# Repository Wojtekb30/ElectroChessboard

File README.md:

# ElectroChessboard
Electronic chessboard

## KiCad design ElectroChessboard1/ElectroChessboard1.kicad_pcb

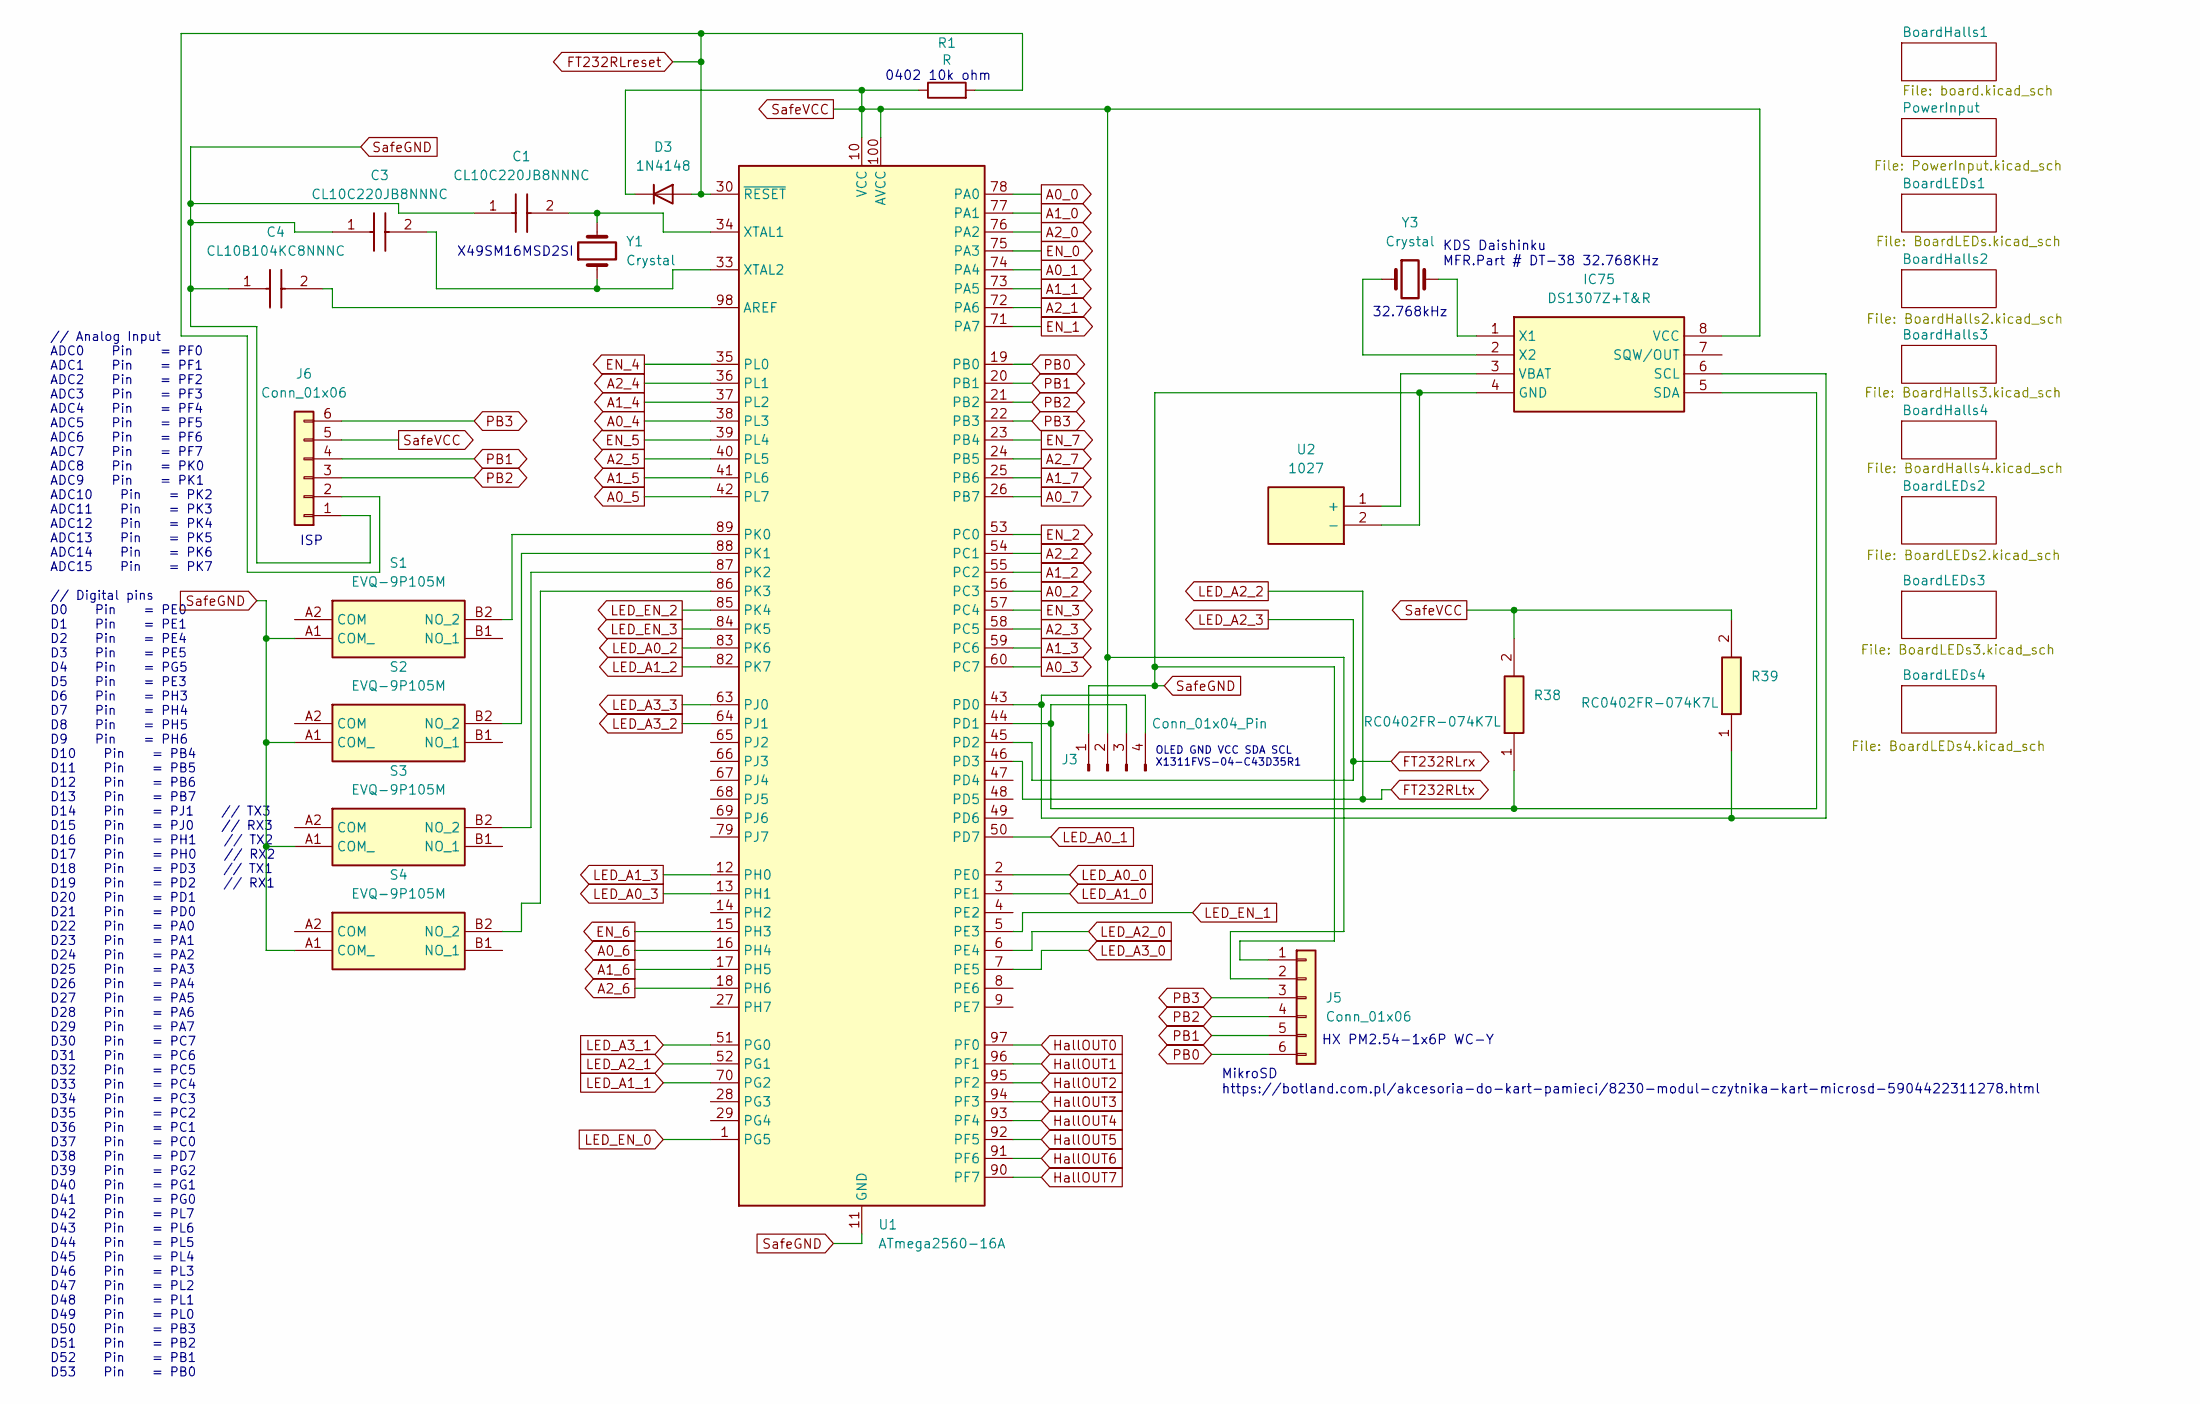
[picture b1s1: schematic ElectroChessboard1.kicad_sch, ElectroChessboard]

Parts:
C1, C3: CL10C220JB8NNNC; CAPC1608X90N; Mouser Part Number 187-CL10C220JB8NNNC
C4: CL10B104KC8NNNC; CAPC1608X90N; Mouser Part Number 187-CL10B104KC8NNNC
D3: 1N4148; D_SOD-123
IC75: DS1307Z+T&R; SOIC127P600X175-8N; Mouser Part Number 700-DS1307ZT&R
J3: Conn_01x04_Pin; PinSocket_1x04_P1.27mm_Vertical_SMD_Pin1Right
J5: Conn_01x06; PinSocket_1x06_P2.54mm_Horizontal
J6: Conn_01x06; PinSocket_1x06_P2.00mm_Vertical_SMD_Pin1Right
R1: R; R_0402_1005Metric
R38, R39: RC0402FR-074K7L; RESC1005X40N; Manufacturer_Part_Number RC0402FR-074K7L; Mouser Part Number 603-RC0402FR-074K7L
S1, S2, S3, S4: EVQ-9P105M; EVQ9P105M; Mouser Part Number 667-EVQ-9P105M
U1: ATmega2560-16A; TQFP-100_14x14mm_P0.5mm
U2: 1027; Mouser Part Number 534-1027
Y1: Crystal; Crystal_SMD_HC49-SD
Y3: Crystal; Crystal_C38-LF_D3.0mm_L8.0mm_Vertical

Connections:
A0_0: U1.78 (PA0); also elsewhere on the board
A0_1: U1.74 (PA4); also elsewhere on the board
A0_2: U1.56 (PC3); also elsewhere on the board
A0_3: U1.60 (PC7); also elsewhere on the board
A0_4: U1.38 (PL3); also elsewhere on the board
A0_5: U1.42 (PL7); also elsewhere on the board
A0_6: U1.16 (PH4); also elsewhere on the board
A0_7: U1.26 (PB7); also elsewhere on the board
A1_0: U1.77 (PA1); also elsewhere on the board
A1_1: U1.73 (PA5); also elsewhere on the board
A1_2: U1.55 (PC2); also elsewhere on the board
A1_3: U1.59 (PC6); also elsewhere on the board
A1_4: U1.37 (PL2); also elsewhere on the board
A1_5: U1.41 (PL6); also elsewhere on the board
A1_6: U1.17 (PH5); also elsewhere on the board
A1_7: U1.25 (PB6); also elsewhere on the board
A2_0: U1.76 (PA2); also elsewhere on the board
A2_1: U1.72 (PA6); also elsewhere on the board
A2_2: U1.54 (PC1); also elsewhere on the board
A2_3: U1.58 (PC5); also elsewhere on the board
A2_4: U1.36 (PL1); also elsewhere on the board
A2_5: U1.40 (PL5); also elsewhere on the board
A2_6: U1.18 (PH6); also elsewhere on the board
A2_7: U1.24 (PB5); also elsewhere on the board
EN_0: U1.75 (PA3); also elsewhere on the board
EN_1: U1.71 (PA7); also elsewhere on the board
EN_2: U1.53 (PC0); also elsewhere on the board
EN_3: U1.57 (PC4); also elsewhere on the board
EN_4: U1.35 (PL0); also elsewhere on the board
EN_5: U1.39 (PL4); also elsewhere on the board
EN_6: U1.15 (PH3); also elsewhere on the board
EN_7: U1.23 (PB4); also elsewhere on the board
FT232RLreset: D3.2 (A), J6.2, R1.2, U1.30 (~RESET); also elsewhere on the board
HallOUT0: U1.97 (PF0); also elsewhere on the board
HallOUT1: U1.96 (PF1); also elsewhere on the board
HallOUT2: U1.95 (PF2); also elsewhere on the board
HallOUT3: U1.94 (PF3); also elsewhere on the board
HallOUT4: U1.93 (PF4); also elsewhere on the board
HallOUT5: U1.92 (PF5); also elsewhere on the board
HallOUT6: U1.91 (PF6); also elsewhere on the board
HallOUT7: U1.90 (PF7); also elsewhere on the board
LED_A0_0: U1.2 (PE0); also elsewhere on the board
LED_A0_1: U1.50 (PD7); also elsewhere on the board
LED_A0_2: U1.83 (PK6); also elsewhere on the board
LED_A0_3: U1.13 (PH1); also elsewhere on the board
LED_A1_0: U1.3 (PE1); also elsewhere on the board
LED_A1_1: U1.70 (PG2); also elsewhere on the board
LED_A1_2: U1.82 (PK7); also elsewhere on the board
LED_A1_3: U1.12 (PH0); also elsewhere on the board
LED_A2_0: U1.6 (PE4); also elsewhere on the board
LED_A2_1: U1.52 (PG1); also elsewhere on the board
LED_A3_0: U1.7 (PE5); also elsewhere on the board
LED_A3_1: U1.51 (PG0); also elsewhere on the board
LED_A3_2: U1.64 (PJ1); also elsewhere on the board
LED_A3_3: U1.63 (PJ0); also elsewhere on the board
LED_EN_0: U1.1 (PG5); also elsewhere on the board
LED_EN_1: U1.5 (PE3); also elsewhere on the board
LED_EN_2: U1.85 (PK4); also elsewhere on the board
LED_EN_3: U1.84 (PK5); also elsewhere on the board
unnamed: IC75.6 (SCL), J3.4, R39.1, U1.43 (PD0)
unnamed: IC75.5 (SDA), J3.3, R38.1, U1.44 (PD1)
unnamed: IC75.3 (VBAT), U2.1 (+)
unnamed: IC75.1 (X1), Y3.2
unnamed: IC75.2 (X2), Y3.1
unnamed: S1.B2 (NO_2), U1.89 (PK0)
unnamed: S2.B2 (NO_2), U1.88 (PK1)
unnamed: S3.B2 (NO_2), U1.87 (PK2)
unnamed: S4.B2 (NO_2), U1.86 (PK3)
unnamed: C4.2, U1.98 (AREF)
unnamed: C1.2, U1.34 (XTAL1), Y1.2
unnamed: C3.2, U1.33 (XTAL2), Y1.1
PB0: J5.6, U1.19 (PB0)
PB1: J5.5, J6.4, U1.20 (PB1)
PB2: J5.4, J6.3, U1.21 (PB2)
PB3: J5.3, J6.6, U1.22 (PB3)
SafeGND: C1.1, C3.1, C4.1, IC75.4 (GND), J3.1, J5.1, J6.1, S1.A1 (COM_), S2.A1 (COM_), S3.A1 (COM_), S4.A1 (COM_), U1.11 (GND), U1.32 (GND), U1.62 (GND), U1.81 (GND), U1.99 (GND), U2.2 (-); also elsewhere on the board
SafeVCC: D3.1 (K), IC75.8 (VCC), J3.2, J5.2, J6.5, R1.1, R38.2, R39.2, U1.10 (VCC), U1.31 (VCC), U1.61 (VCC), U1.80 (VCC), U1.100 (AVCC); also elsewhere on the board

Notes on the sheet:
// Analog Input ADC0 Pin = PF0 ADC1 Pin = PF1 ADC2 Pin = PF2 ADC3 Pin = PF3 ADC4 Pin = PF4 ADC5 Pin = PF5 ADC6 Pin = PF6 ADC7 Pin = PF7 ADC8 Pin = PK0 ADC9 Pin = PK1 ADC10 Pin = PK2 ADC11 Pin = PK3 ADC12 Pin = PK4 ADC13 Pin = PK5 ADC14 Pin = PK6 ADC15 Pin = PK7 // Digital pins D0 Pin = PE0 D1 Pin =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
32.768kHz
X49SM16MSD2SI
0402 10k ohm
MikroSD https://botland.com.pl/akcesoria-do-kart-pamieci/8230-modul-czytnika-kart-microsd-5904422311278.html
ISP
HX PM2.54-1x6P WC-Y
KDS Daishinku MFR.Part # DT-38 32.768KHz
OLED GND VCC SDA SCL X1311FVS-04-C43D35R1

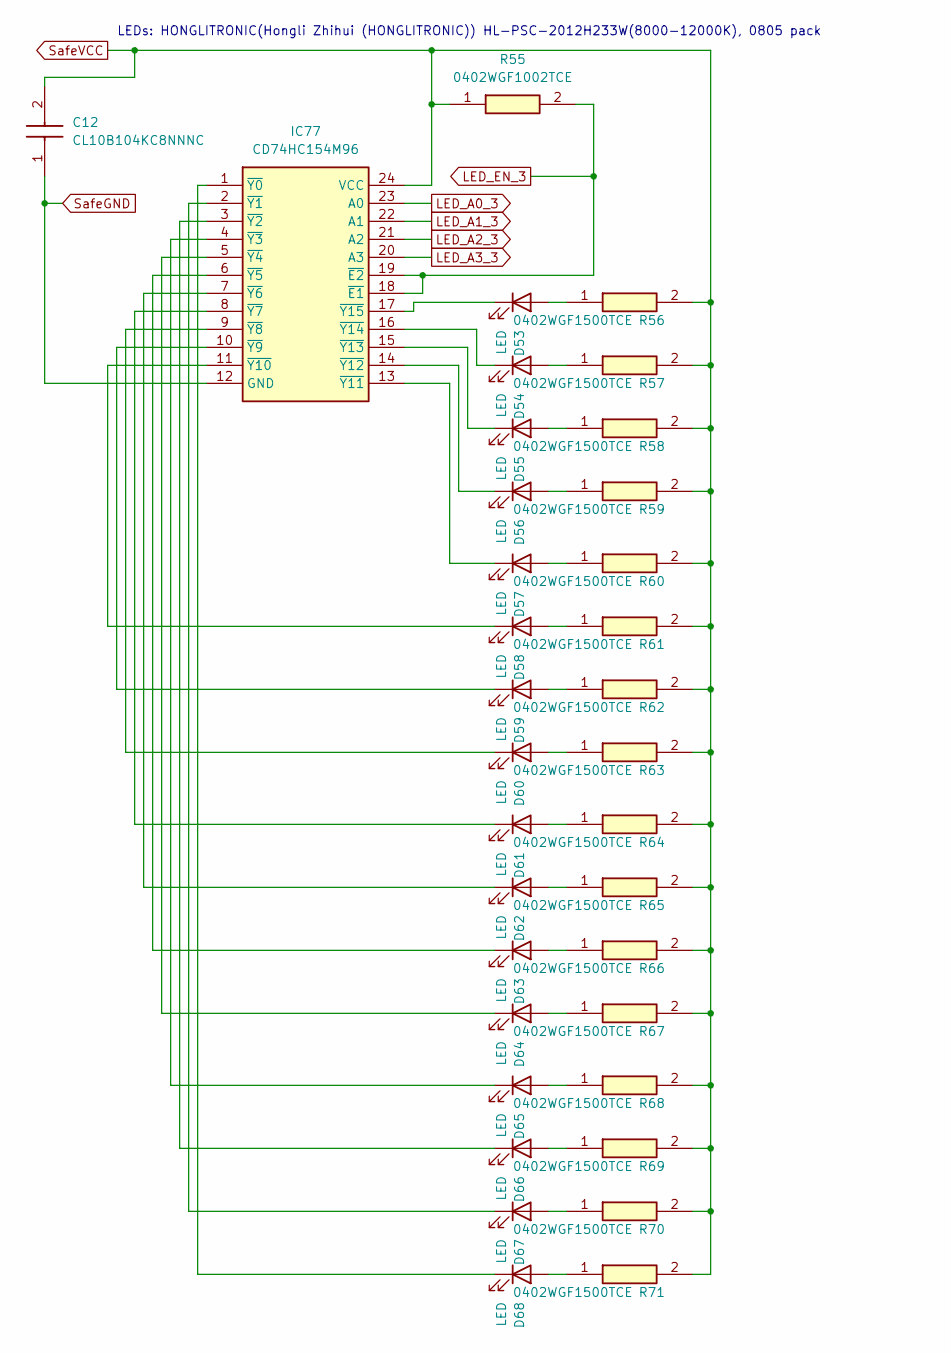
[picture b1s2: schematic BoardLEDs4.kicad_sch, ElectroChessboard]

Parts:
C12: CL10B104KC8NNNC; CAPC1608X90N; Mouser Part Number 187-CL10B104KC8NNNC
D53, D54, D55, D56, D57, D58, D59, D60, D61, D62, D63, D64, D65, D66, D67, D68: LED; LED_0805_2012Metric
IC77: CD74HC154M96; SOIC127P1030X265-24N; Mouser Part Number 595-CD74HC154M96
R55: 0402WGF1002TCE; RESC1005X40N; Mouser Part Number 303-0402WGF1002TCE
R56, R57, R58, R59, R60, R61, R62, R63, R64, R65, R66, R67, R68, R69, R70, R71: 0402WGF1500TCE; RESC1005X40N; Manufacturer_Part_Number 0402WGF1500TCE

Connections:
LED_A0_3: IC77.23 (A0); also elsewhere on the board
LED_A1_3: IC77.22 (A1); also elsewhere on the board
LED_A3_3: IC77.20 (A3); also elsewhere on the board
LED_EN_3: IC77.18 (~E1), IC77.19 (~E2), R55.2; also elsewhere on the board
unnamed: D53.2 (A), R56.1
unnamed: D53.1 (K), IC77.17 (~Y15)
unnamed: D54.2 (A), R57.1
unnamed: D54.1 (K), IC77.16 (~Y14)
unnamed: D55.2 (A), R58.1
unnamed: D55.1 (K), IC77.15 (~Y13)
unnamed: D56.2 (A), R59.1
unnamed: D56.1 (K), IC77.14 (~Y12)
unnamed: D57.2 (A), R60.1
unnamed: D57.1 (K), IC77.13 (~Y11)
unnamed: D58.2 (A), R61.1
unnamed: D58.1 (K), IC77.11 (~Y10)
unnamed: D59.2 (A), R62.1
unnamed: D59.1 (K), IC77.10 (~Y9)
unnamed: D60.2 (A), R63.1
unnamed: D60.1 (K), IC77.9 (~Y8)
unnamed: D61.2 (A), R64.1
unnamed: D61.1 (K), IC77.8 (~Y7)
unnamed: D62.2 (A), R65.1
unnamed: D62.1 (K), IC77.7 (~Y6)
unnamed: D63.2 (A), R66.1
unnamed: D63.1 (K), IC77.6 (~Y5)
unnamed: D64.2 (A), R67.1
unnamed: D64.1 (K), IC77.5 (~Y4)
unnamed: D65.2 (A), R68.1
unnamed: D65.1 (K), IC77.4 (~Y3)
unnamed: D66.2 (A), R69.1
unnamed: D66.1 (K), IC77.3 (~Y2)
unnamed: D67.2 (A), R70.1
unnamed: D67.1 (K), IC77.2 (~Y1)
unnamed: D68.2 (A), R71.1
unnamed: D68.1 (K), IC77.1 (~Y0)
SafeGND: C12.1, IC77.12 (GND); also elsewhere on the board
SafeVCC: C12.2, IC77.24 (VCC), R55.1, R56.2, R57.2, R58.2, R59.2, R60.2, R61.2, R62.2, R63.2, R64.2, R65.2, R66.2, R67.2, R68.2, R69.2, R70.2, R71.2; also elsewhere on the board

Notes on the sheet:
LEDs: HONGLITRONIC(Hongli Zhihui (HONGLITRONIC)) HL-PSC-2012H233W(8000-12000K), 0805 pack

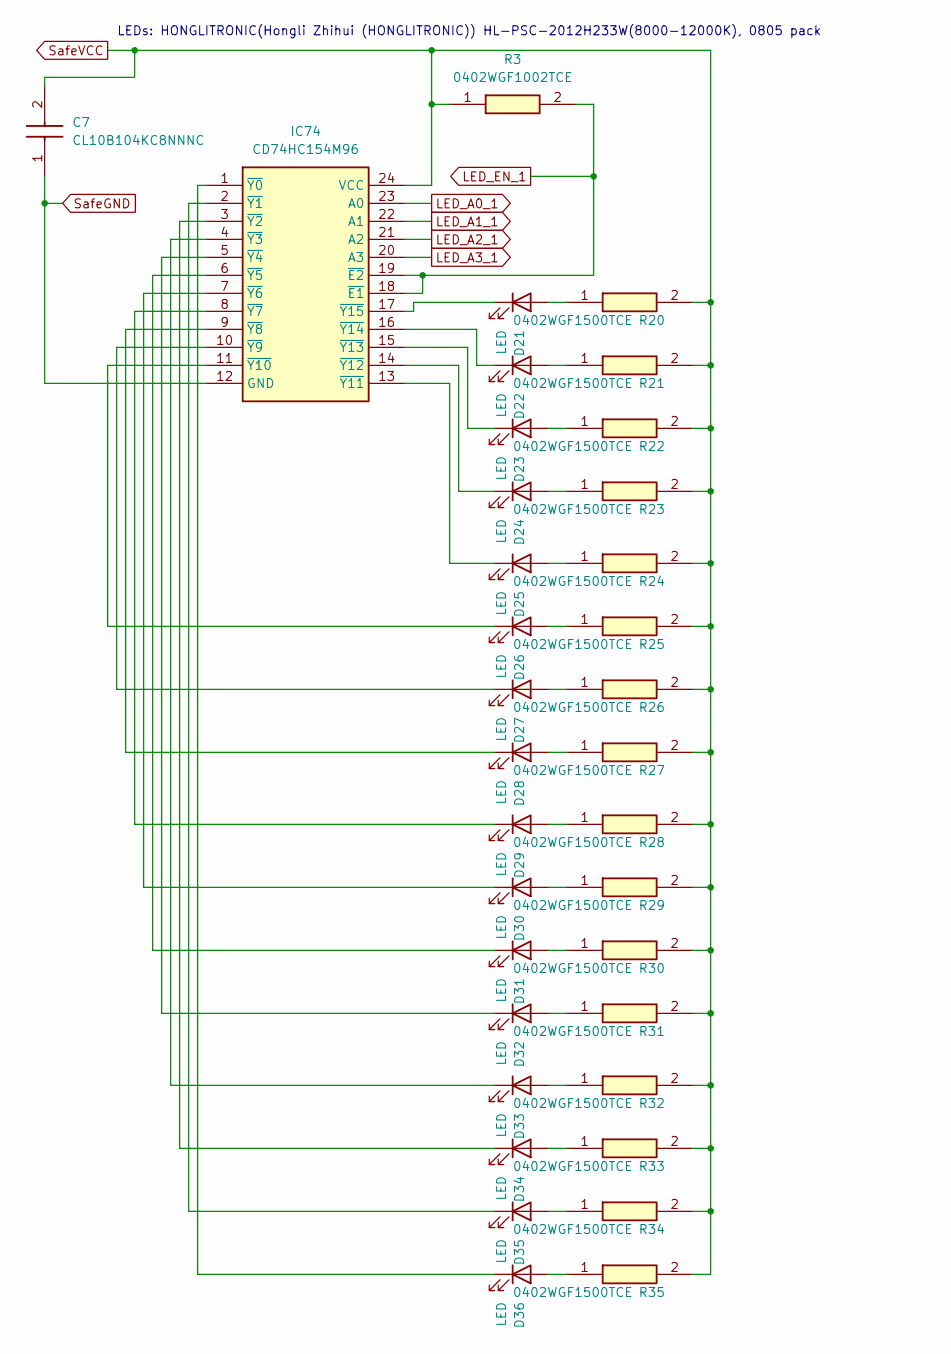
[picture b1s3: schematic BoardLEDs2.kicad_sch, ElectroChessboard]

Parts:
C7: CL10B104KC8NNNC; CAPC1608X90N; Mouser Part Number 187-CL10B104KC8NNNC
D21, D22, D23, D24, D25, D26, D27, D28, D29, D30, D31, D32, D33, D34, D35, D36: LED; LED_0805_2012Metric
IC74: CD74HC154M96; SOIC127P1030X265-24N; Mouser Part Number 595-CD74HC154M96
R3: 0402WGF1002TCE; RESC1005X40N; Mouser Part Number 303-0402WGF1002TCE
R20, R21, R22, R23, R24, R25, R26, R27, R28, R29, R30, R31, R32, R33, R34, R35: 0402WGF1500TCE; RESC1005X40N; Manufacturer_Part_Number 0402WGF1500TCE

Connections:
LED_A0_1: IC74.23 (A0); also elsewhere on the board
LED_A1_1: IC74.22 (A1); also elsewhere on the board
LED_A2_1: IC74.21 (A2); also elsewhere on the board
LED_A3_1: IC74.20 (A3); also elsewhere on the board
LED_EN_1: IC74.18 (~E1), IC74.19 (~E2), R3.2; also elsewhere on the board
unnamed: D21.2 (A), R20.1
unnamed: D21.1 (K), IC74.17 (~Y15)
unnamed: D22.2 (A), R21.1
unnamed: D22.1 (K), IC74.16 (~Y14)
unnamed: D23.2 (A), R22.1
unnamed: D23.1 (K), IC74.15 (~Y13)
unnamed: D24.2 (A), R23.1
unnamed: D24.1 (K), IC74.14 (~Y12)
unnamed: D25.2 (A), R24.1
unnamed: D25.1 (K), IC74.13 (~Y11)
unnamed: D26.2 (A), R25.1
unnamed: D26.1 (K), IC74.11 (~Y10)
unnamed: D27.2 (A), R26.1
unnamed: D27.1 (K), IC74.10 (~Y9)
unnamed: D28.2 (A), R27.1
unnamed: D28.1 (K), IC74.9 (~Y8)
unnamed: D29.2 (A), R28.1
unnamed: D29.1 (K), IC74.8 (~Y7)
unnamed: D30.2 (A), R29.1
unnamed: D30.1 (K), IC74.7 (~Y6)
unnamed: D31.2 (A), R30.1
unnamed: D31.1 (K), IC74.6 (~Y5)
unnamed: D32.2 (A), R31.1
unnamed: D32.1 (K), IC74.5 (~Y4)
unnamed: D33.2 (A), R32.1
unnamed: D33.1 (K), IC74.4 (~Y3)
unnamed: D34.2 (A), R33.1
unnamed: D34.1 (K), IC74.3 (~Y2)
unnamed: D35.2 (A), R34.1
unnamed: D35.1 (K), IC74.2 (~Y1)
unnamed: D36.2 (A), R35.1
unnamed: D36.1 (K), IC74.1 (~Y0)
SafeGND: C7.1, IC74.12 (GND); also elsewhere on the board
SafeVCC: C7.2, IC74.24 (VCC), R3.1, R20.2, R21.2, R22.2, R23.2, R24.2, R25.2, R26.2, R27.2, R28.2, R29.2, R30.2, R31.2, R32.2, R33.2, R34.2, R35.2; also elsewhere on the board

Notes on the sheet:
LEDs: HONGLITRONIC(Hongli Zhihui (HONGLITRONIC)) HL-PSC-2012H233W(8000-12000K), 0805 pack

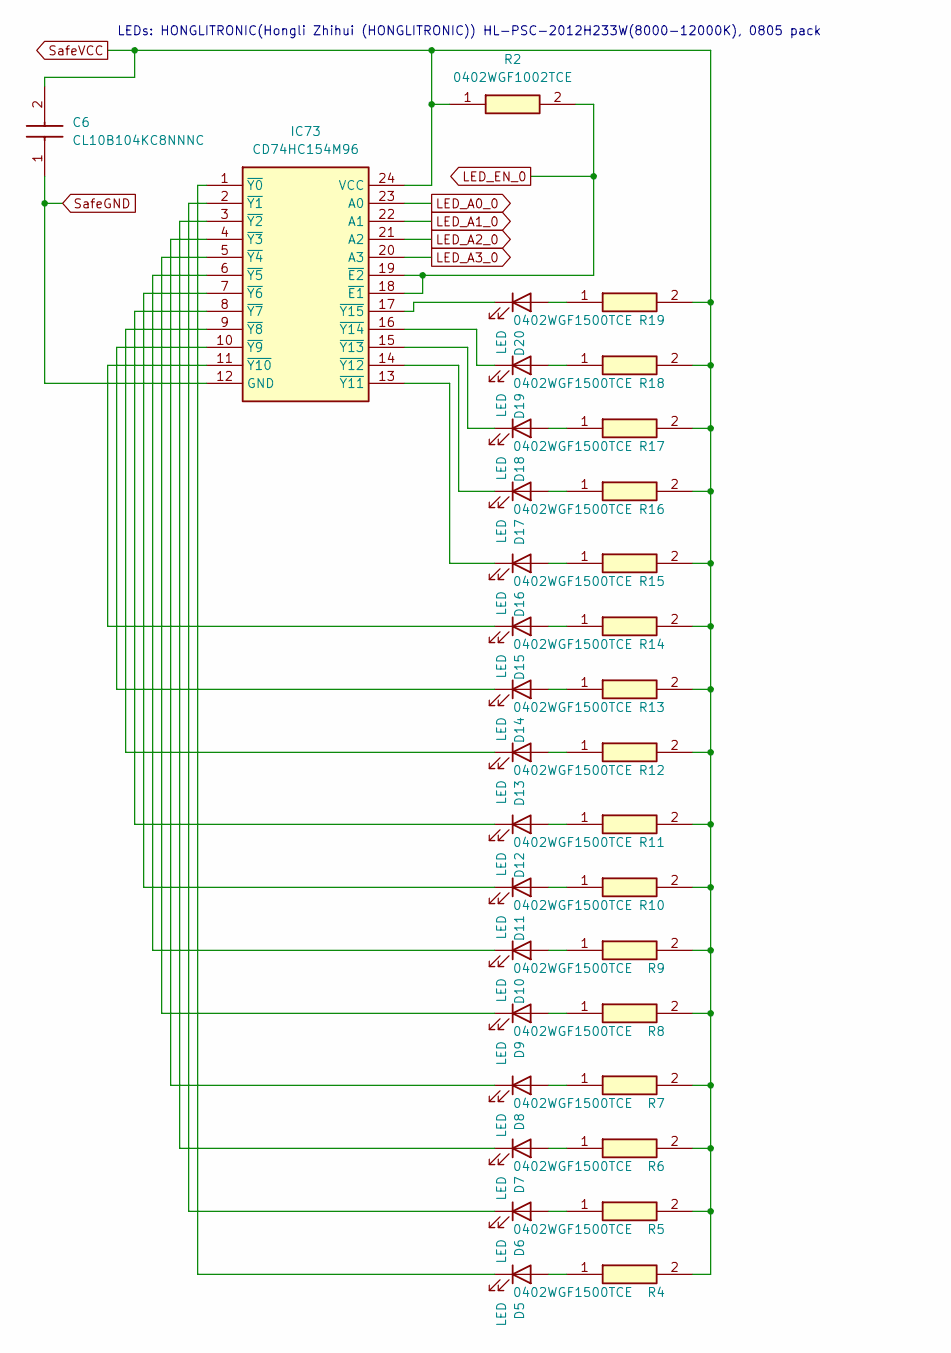
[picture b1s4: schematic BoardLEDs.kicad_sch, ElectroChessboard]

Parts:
C6: CL10B104KC8NNNC; CAPC1608X90N; Mouser Part Number 187-CL10B104KC8NNNC
D5, D6, D7, D8, D9, D10, D11, D12, D13, D14, D15, D16, D17, D18, D19, D20: LED; LED_0805_2012Metric
IC73: CD74HC154M96; SOIC127P1030X265-24N; Mouser Part Number 595-CD74HC154M96
R2: 0402WGF1002TCE; RESC1005X40N; Mouser Part Number 303-0402WGF1002TCE
R4, R5, R6, R7, R8, R9, R10, R11, R12, R13, R14, R15, R16, R17, R18, R19: 0402WGF1500TCE; RESC1005X40N; Manufacturer_Part_Number 0402WGF1500TCE

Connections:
LED_A0_0: IC73.23 (A0); also elsewhere on the board
LED_A1_0: IC73.22 (A1); also elsewhere on the board
LED_A2_0: IC73.21 (A2); also elsewhere on the board
LED_A3_0: IC73.20 (A3); also elsewhere on the board
LED_EN_0: IC73.18 (~E1), IC73.19 (~E2), R2.2; also elsewhere on the board
unnamed: D5.2 (A), R4.1
unnamed: D5.1 (K), IC73.1 (~Y0)
unnamed: D6.2 (A), R5.1
unnamed: D6.1 (K), IC73.2 (~Y1)
unnamed: D7.2 (A), R6.1
unnamed: D7.1 (K), IC73.3 (~Y2)
unnamed: D8.2 (A), R7.1
unnamed: D8.1 (K), IC73.4 (~Y3)
unnamed: D9.2 (A), R8.1
unnamed: D9.1 (K), IC73.5 (~Y4)
unnamed: D10.2 (A), R9.1
unnamed: D10.1 (K), IC73.6 (~Y5)
unnamed: D11.2 (A), R10.1
unnamed: D11.1 (K), IC73.7 (~Y6)
unnamed: D12.2 (A), R11.1
unnamed: D12.1 (K), IC73.8 (~Y7)
unnamed: D13.2 (A), R12.1
unnamed: D13.1 (K), IC73.9 (~Y8)
unnamed: D14.2 (A), R13.1
unnamed: D14.1 (K), IC73.10 (~Y9)
unnamed: D15.2 (A), R14.1
unnamed: D15.1 (K), IC73.11 (~Y10)
unnamed: D16.2 (A), R15.1
unnamed: D16.1 (K), IC73.13 (~Y11)
unnamed: D17.2 (A), R16.1
unnamed: D17.1 (K), IC73.14 (~Y12)
unnamed: D18.2 (A), R17.1
unnamed: D18.1 (K), IC73.15 (~Y13)
unnamed: D19.2 (A), R18.1
unnamed: D19.1 (K), IC73.16 (~Y14)
unnamed: D20.2 (A), R19.1
unnamed: D20.1 (K), IC73.17 (~Y15)
SafeGND: C6.1, IC73.12 (GND); also elsewhere on the board
SafeVCC: C6.2, IC73.24 (VCC), R2.1, R4.2, R5.2, R6.2, R7.2, R8.2, R9.2, R10.2, R11.2, R12.2, R13.2, R14.2, R15.2, R16.2, R17.2, R18.2, R19.2; also elsewhere on the board

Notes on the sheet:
LEDs: HONGLITRONIC(Hongli Zhihui (HONGLITRONIC)) HL-PSC-2012H233W(8000-12000K), 0805 pack

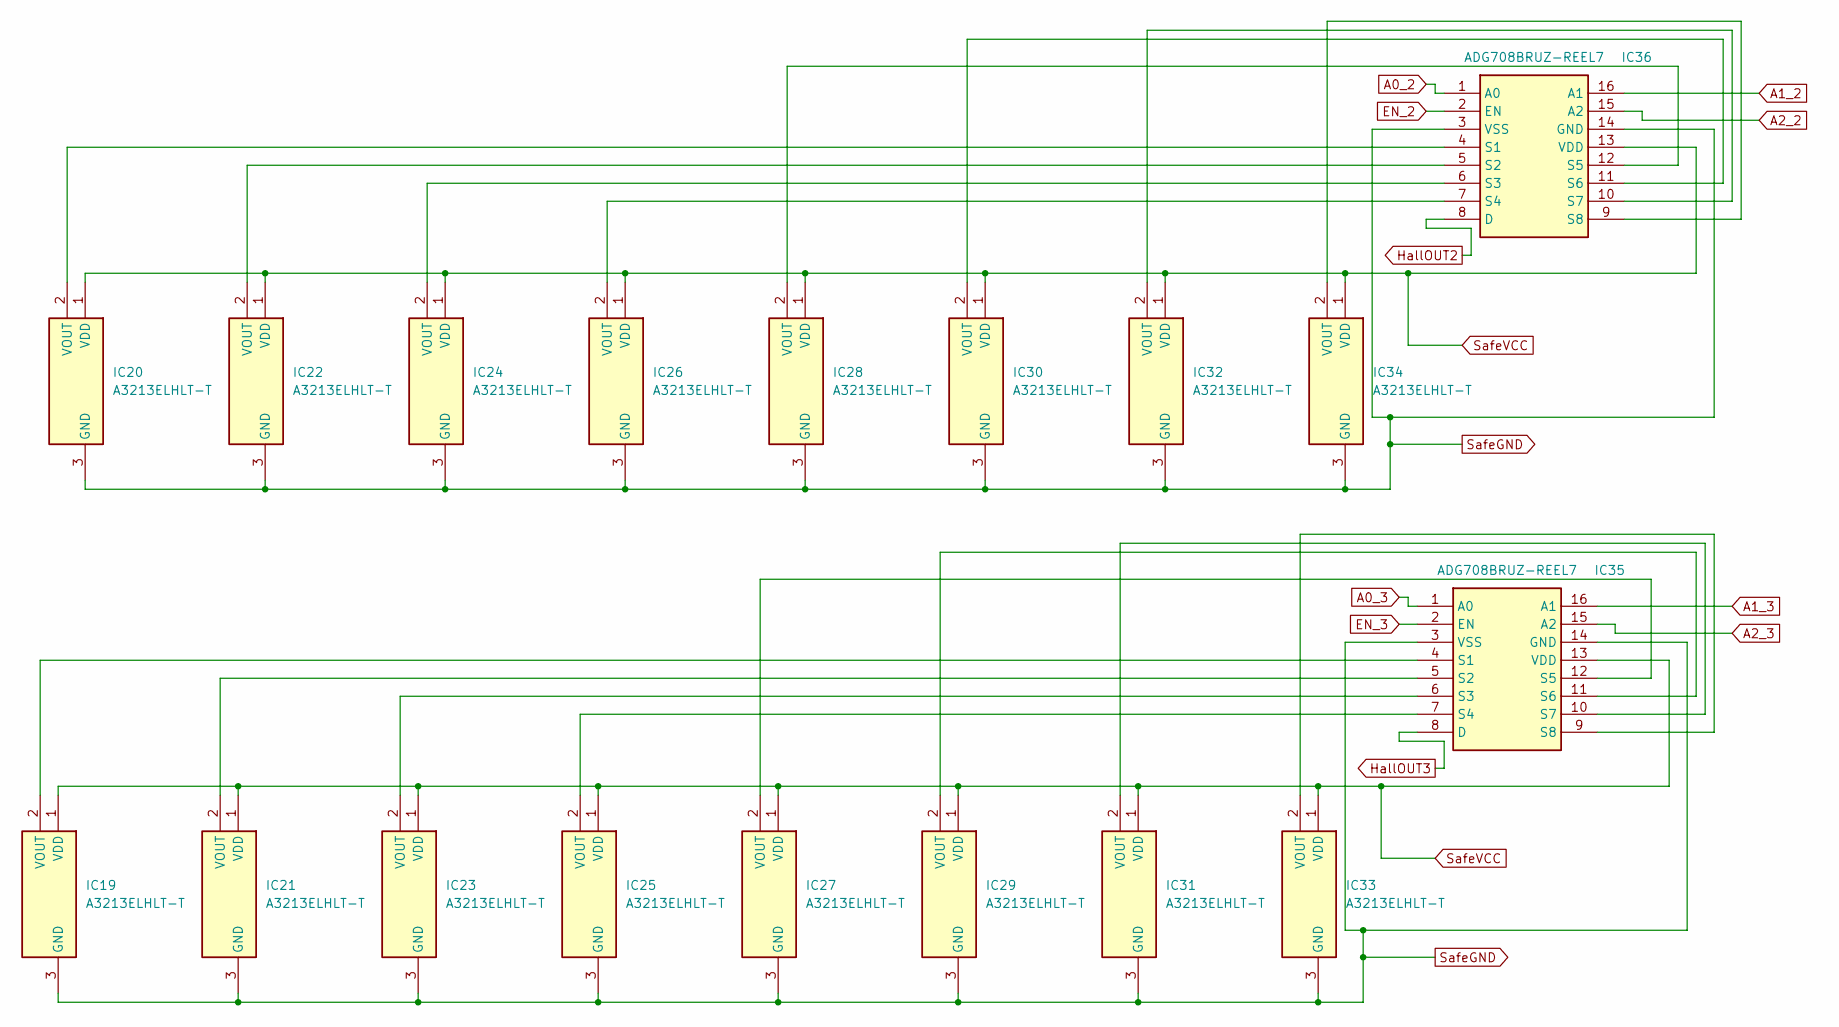
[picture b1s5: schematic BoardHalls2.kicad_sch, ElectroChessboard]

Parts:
IC19, IC20, IC21, IC22, IC23, IC24, IC25, IC26, IC27, IC28, IC29, IC30, IC31, IC32, IC33, IC34: A3213ELHLT-T; A3213ELHLTT; Mouser Part Number 250-A3213ELHLT-T
IC35, IC36: ADG708BRUZ-REEL7; SOP65P640X120-16N; Mouser Part Number 584-ADG708BRUZ-R7

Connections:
A0_2: IC36.1 (A0); also elsewhere on the board
A0_3: IC35.1 (A0); also elsewhere on the board
A1_2: IC36.16 (A1); also elsewhere on the board
A1_3: IC35.16 (A1); also elsewhere on the board
A2_2: IC36.15 (A2); also elsewhere on the board
A2_3: IC35.15 (A2); also elsewhere on the board
EN_2: IC36.2 (EN); also elsewhere on the board
EN_3: IC35.2 (EN); also elsewhere on the board
HallOUT2: IC36.8 (D); also elsewhere on the board
HallOUT3: IC35.8 (D); also elsewhere on the board
unnamed: IC19.2 (VOUT), IC35.4 (S1)
unnamed: IC20.2 (VOUT), IC36.4 (S1)
unnamed: IC21.2 (VOUT), IC35.5 (S2)
unnamed: IC22.2 (VOUT), IC36.5 (S2)
unnamed: IC23.2 (VOUT), IC35.6 (S3)
unnamed: IC24.2 (VOUT), IC36.6 (S3)
unnamed: IC25.2 (VOUT), IC35.7 (S4)
unnamed: IC26.2 (VOUT), IC36.7 (S4)
unnamed: IC27.2 (VOUT), IC35.12 (S5)
unnamed: IC28.2 (VOUT), IC36.12 (S5)
unnamed: IC29.2 (VOUT), IC35.11 (S6)
unnamed: IC30.2 (VOUT), IC36.11 (S6)
unnamed: IC31.2 (VOUT), IC35.10 (S7)
unnamed: IC32.2 (VOUT), IC36.10 (S7)
unnamed: IC33.2 (VOUT), IC35.9 (S8)
unnamed: IC34.2 (VOUT), IC36.9 (S8)
SafeGND: IC19.3 (GND), IC20.3 (GND), IC21.3 (GND), IC22.3 (GND), IC23.3 (GND), IC24.3 (GND), IC25.3 (GND), IC26.3 (GND), IC27.3 (GND), IC28.3 (GND), IC29.3 (GND), IC30.3 (GND), IC31.3 (GND), IC32.3 (GND), IC33.3 (GND), IC34.3 (GND), IC35.3 (VSS), IC35.14 (GND), IC36.3 (VSS), IC36.14 (GND); also elsewhere on the board
SafeVCC: IC19.1 (VDD), IC20.1 (VDD), IC21.1 (VDD), IC22.1 (VDD), IC23.1 (VDD), IC24.1 (VDD), IC25.1 (VDD), IC26.1 (VDD), IC27.1 (VDD), IC28.1 (VDD), IC29.1 (VDD), IC30.1 (VDD), IC31.1 (VDD), IC32.1 (VDD), IC33.1 (VDD), IC34.1 (VDD), IC35.13 (VDD), IC36.13 (VDD); also elsewhere on the board

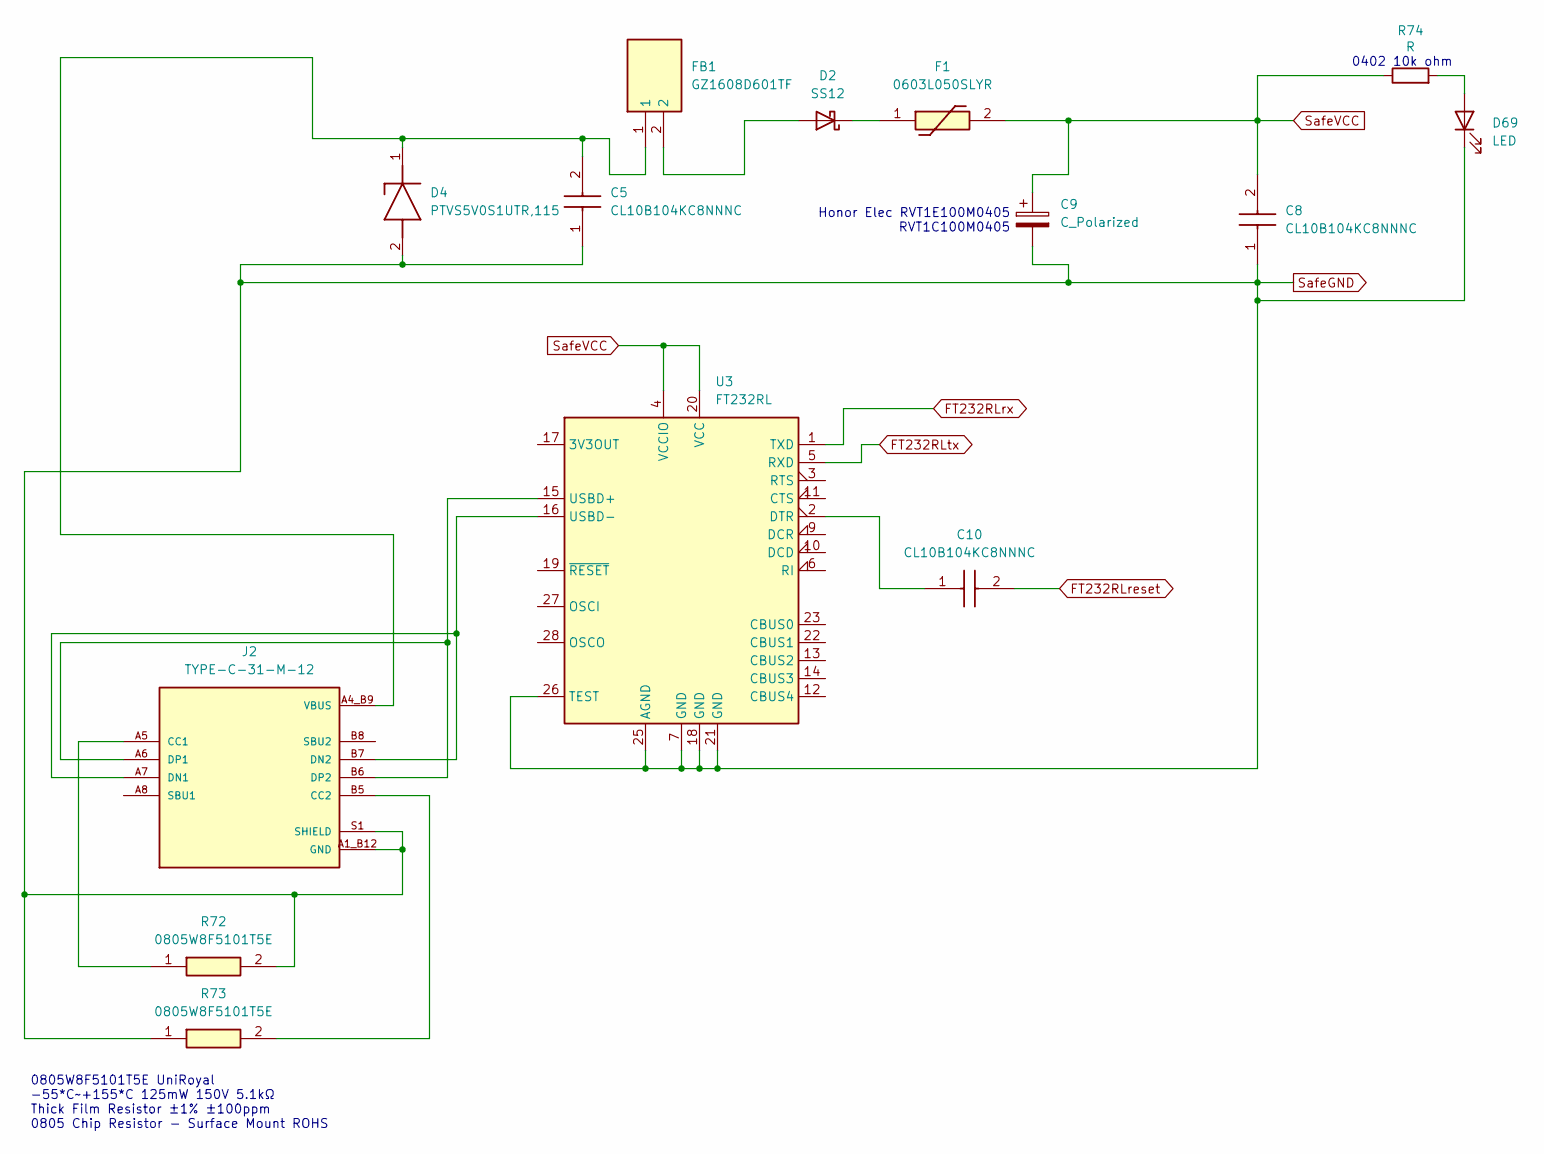
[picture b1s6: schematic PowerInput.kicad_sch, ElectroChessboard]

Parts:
C5, C8, C10: CL10B104KC8NNNC; CAPC1608X90N; Mouser Part Number 187-CL10B104KC8NNNC
C9: C_Polarized; CP_Elec_4x5.4
D2: SS12; D_SMA
D4: PTVS5V0S1UTR,115; SOD123W; Mouser Part Number 771-PTVS5V0S1UTR115
D69: LED; LED_0805_2012Metric
F1: 0603L050SLYR; Mouser Part Number 576-0603L050SLYR
FB1: GZ1608D601TF; BEADC1608X95N; Manufacturer_Part_Number GZ1608D601TF
J2: TYPE-C-31-M-12; HRO_TYPE-C-31-M-12; PARTREV 2020.12.08
R72, R73: 0805W8F5101T5E; RESC2013X65N; Manufacturer_Part_Number 0805W8F5101T5E
R74: R; R_0402_1005Metric
U3: FT232RL; SSOP-28_5.3x10.2mm_P0.65mm

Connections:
FT232RLreset: C10.2; also elsewhere on the board
unnamed: D2.2 (A), FB1.2
unnamed: D2.1 (K), F1.1
unnamed: D69.2 (A), R74.2
unnamed: J2.A5 (CC1), R72.1
unnamed: J2.B5 (CC2), R73.2
unnamed: J2.A7 (DN1), J2.B7 (DN2), U3.16 (USBD-)
unnamed: J2.A6 (DP1), J2.B6 (DP2), U3.15 (USBD+)
unnamed: C10.1, U3.2 (DTR)
SafeGND: C5.1, C8.1, C9.2, D4.2 (A), D69.1 (K), J2.A1_B12 (GND), J2.B1_A12 (GND), J2.S1 (SHIELD), J2.S2 (SHIELD), J2.S3 (SHIELD), J2.S4 (SHIELD), R72.2, R73.1, U3.7 (GND), U3.18 (GND), U3.21 (GND), U3.25 (AGND), U3.26 (TEST); also elsewhere on the board
SafeVCC: C8.2, C9.1, F1.2, R74.1, U3.4 (VCCIO), U3.20 (VCC); also elsewhere on the board
VBUS: C5.2, D4.1 (K), FB1.1, J2.A4_B9 (VBUS), J2.B4_A9 (VBUS)

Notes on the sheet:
0402 10k ohm
Honor Elec RVT1E100M0405 RVT1C100M0405
0805W8F5101T5E UniRoyal -55*C~+155*C 125mW 150V 5.1kΩ Thick Film Resistor ±1% ±100ppm 0805 Chip Resistor - Surface Mount ROHS

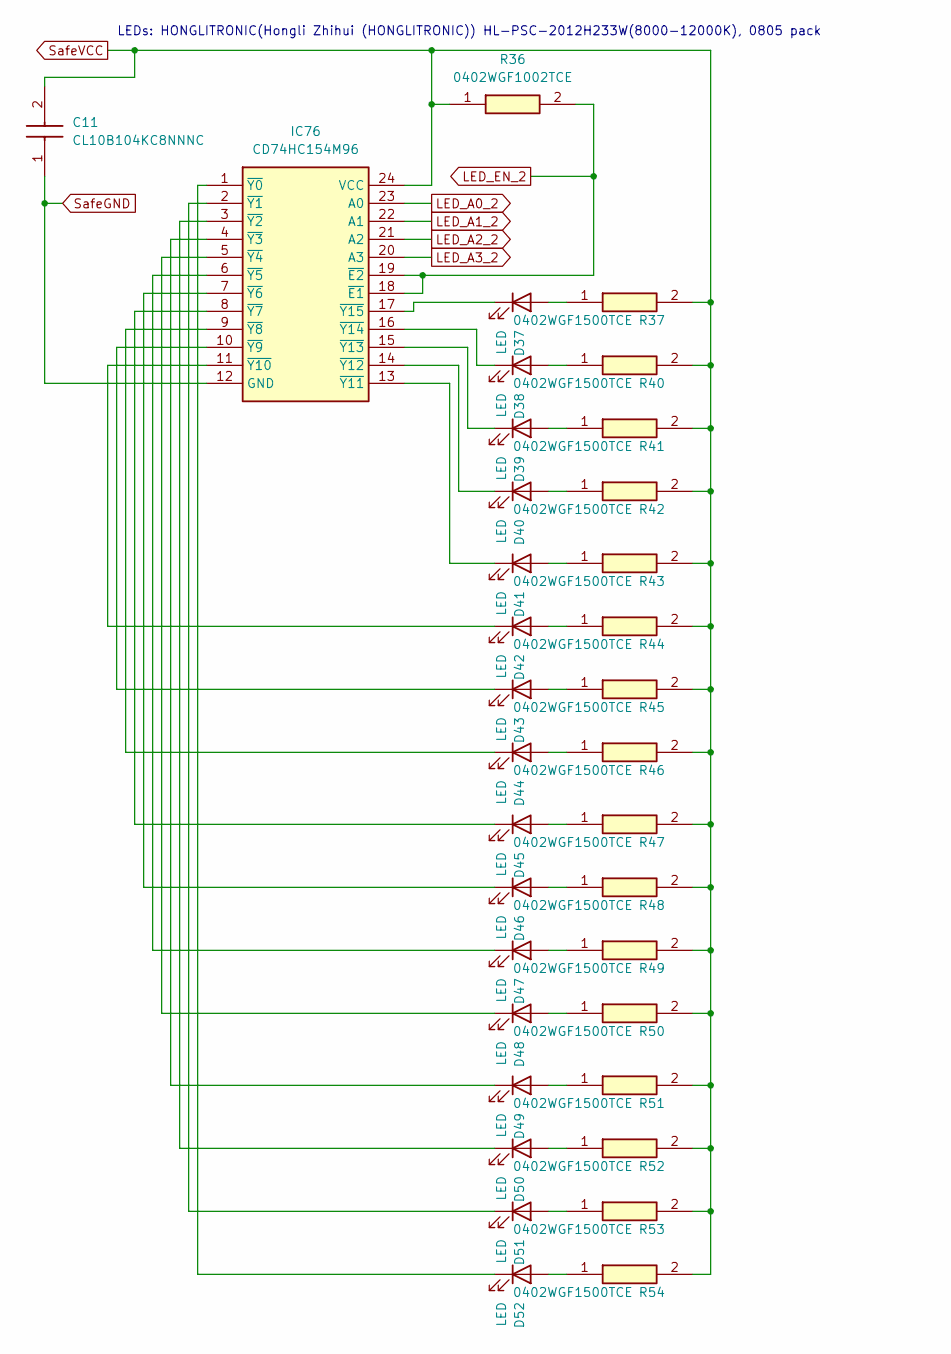
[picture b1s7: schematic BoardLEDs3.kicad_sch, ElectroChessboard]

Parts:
C11: CL10B104KC8NNNC; CAPC1608X90N; Mouser Part Number 187-CL10B104KC8NNNC
D37, D38, D39, D40, D41, D42, D43, D44, D45, D46, D47, D48, D49, D50, D51, D52: LED; LED_0805_2012Metric
IC76: CD74HC154M96; SOIC127P1030X265-24N; Mouser Part Number 595-CD74HC154M96
R36: 0402WGF1002TCE; RESC1005X40N; Mouser Part Number 303-0402WGF1002TCE
R37, R40, R41, R42, R43, R44, R45, R46, R47, R48, R49, R50, R51, R52, R53, R54: 0402WGF1500TCE; RESC1005X40N; Manufacturer_Part_Number 0402WGF1500TCE

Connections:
LED_A0_2: IC76.23 (A0); also elsewhere on the board
LED_A1_2: IC76.22 (A1); also elsewhere on the board
LED_A3_2: IC76.20 (A3); also elsewhere on the board
LED_EN_2: IC76.18 (~E1), IC76.19 (~E2), R36.2; also elsewhere on the board
unnamed: D37.2 (A), R37.1
unnamed: D37.1 (K), IC76.17 (~Y15)
unnamed: D38.2 (A), R40.1
unnamed: D38.1 (K), IC76.16 (~Y14)
unnamed: D39.2 (A), R41.1
unnamed: D39.1 (K), IC76.15 (~Y13)
unnamed: D40.2 (A), R42.1
unnamed: D40.1 (K), IC76.14 (~Y12)
unnamed: D41.2 (A), R43.1
unnamed: D41.1 (K), IC76.13 (~Y11)
unnamed: D42.2 (A), R44.1
unnamed: D42.1 (K), IC76.11 (~Y10)
unnamed: D43.2 (A), R45.1
unnamed: D43.1 (K), IC76.10 (~Y9)
unnamed: D44.2 (A), R46.1
unnamed: D44.1 (K), IC76.9 (~Y8)
unnamed: D45.2 (A), R47.1
unnamed: D45.1 (K), IC76.8 (~Y7)
unnamed: D46.2 (A), R48.1
unnamed: D46.1 (K), IC76.7 (~Y6)
unnamed: D47.2 (A), R49.1
unnamed: D47.1 (K), IC76.6 (~Y5)
unnamed: D48.2 (A), R50.1
unnamed: D48.1 (K), IC76.5 (~Y4)
unnamed: D49.2 (A), R51.1
unnamed: D49.1 (K), IC76.4 (~Y3)
unnamed: D50.2 (A), R52.1
unnamed: D50.1 (K), IC76.3 (~Y2)
unnamed: D51.2 (A), R53.1
unnamed: D51.1 (K), IC76.2 (~Y1)
unnamed: D52.2 (A), R54.1
unnamed: D52.1 (K), IC76.1 (~Y0)
SafeGND: C11.1, IC76.12 (GND); also elsewhere on the board
SafeVCC: C11.2, IC76.24 (VCC), R36.1, R37.2, R40.2, R41.2, R42.2, R43.2, R44.2, R45.2, R46.2, R47.2, R48.2, R49.2, R50.2, R51.2, R52.2, R53.2, R54.2; also elsewhere on the board

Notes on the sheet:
LEDs: HONGLITRONIC(Hongli Zhihui (HONGLITRONIC)) HL-PSC-2012H233W(8000-12000K), 0805 pack
